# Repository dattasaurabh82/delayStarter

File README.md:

# DelayStarter
A small module around 555 timer IC to delay the availability of load voltage to an output with dependency on any uC. 
Useful for current sensitive eletctronic assemblies. 

### Necessary details can be found in the schematic itself.

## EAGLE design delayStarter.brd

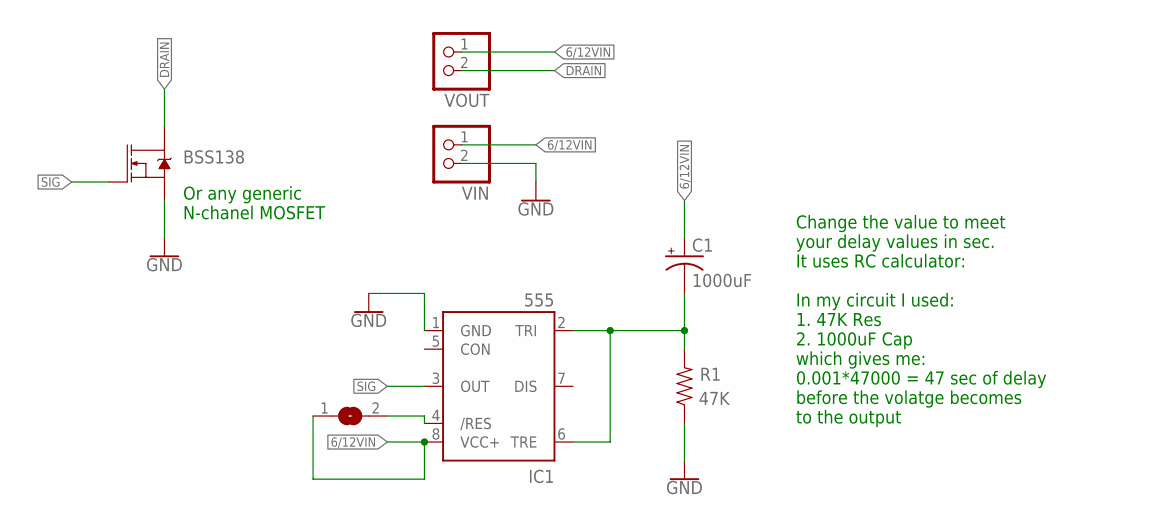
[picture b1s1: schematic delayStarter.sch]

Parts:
BSS138: BSS138; SOT23-3
C1: 1000uF; 153CLV-0810
IC1: 555; SO08
R1: 47K; 0603
SJ1: JUMPER_SJ
VIN: ONBOARDCONTROLINTERFACE_LED-BADGE_SCHEMATIC_ADAFR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; ONBOARDCONTROLINTERFACE_LED-BADGE_SCHEMATIC_ADAFRUIT_JST-PH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
VOUT: ONBOARDCONTROLINTERFACE_LED-BADGE_SCHEMATIC_ADAFR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; ONBOARDCONTROLINTERFACE_LED-BADGE_SCHEMATIC_ADAFRUIT_JST-PH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

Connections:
6/12VIN: C1.+, IC1.8 (VCC+), SJ1.1, VIN.1 (2), VOUT.1 (2)
DRAIN: BSS138.3 (D), VOUT.2 (1)
GND: BSS138.2 (S), IC1.1 (GND), R1.1, VIN.2 (1)
unnamed: C1.-, IC1.2 (TRI), IC1.6 (TRE), R1.2
unnamed: IC1.4 (/RES), SJ1.2
SIG: BSS138.1 (G), IC1.3 (OUT)

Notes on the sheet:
Change the value to meet your delay values in sec. It uses RC calculator: In my circuit I used: 1. 47K Res 2. 1000uF Cap which gives me: 0.001*47000 = 47 sec of delay before the volatge becomes to the output
Or any generic N-chanel MOSFET

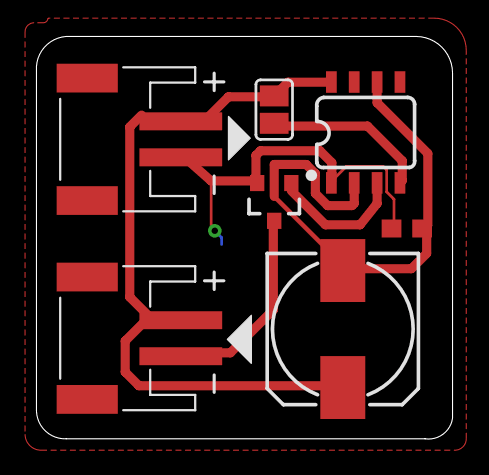
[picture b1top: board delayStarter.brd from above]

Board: 2 copper layers, 23.1 x 22.4 mm, 7 parts (0 on the bottom side), 6 nets.

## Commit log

2020-10-26 first commit ever
2020-10-26 added blank readme

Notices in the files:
parts and their libraries:
SparkFun-IC-Special-Function: Licensing: Creative Commons ShareAlike 4.0 International - https://creativecommons.org/licenses/by-sa/4.0
